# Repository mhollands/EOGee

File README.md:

# EOGee
PCB and code for capturing electrooculograms (EOG).

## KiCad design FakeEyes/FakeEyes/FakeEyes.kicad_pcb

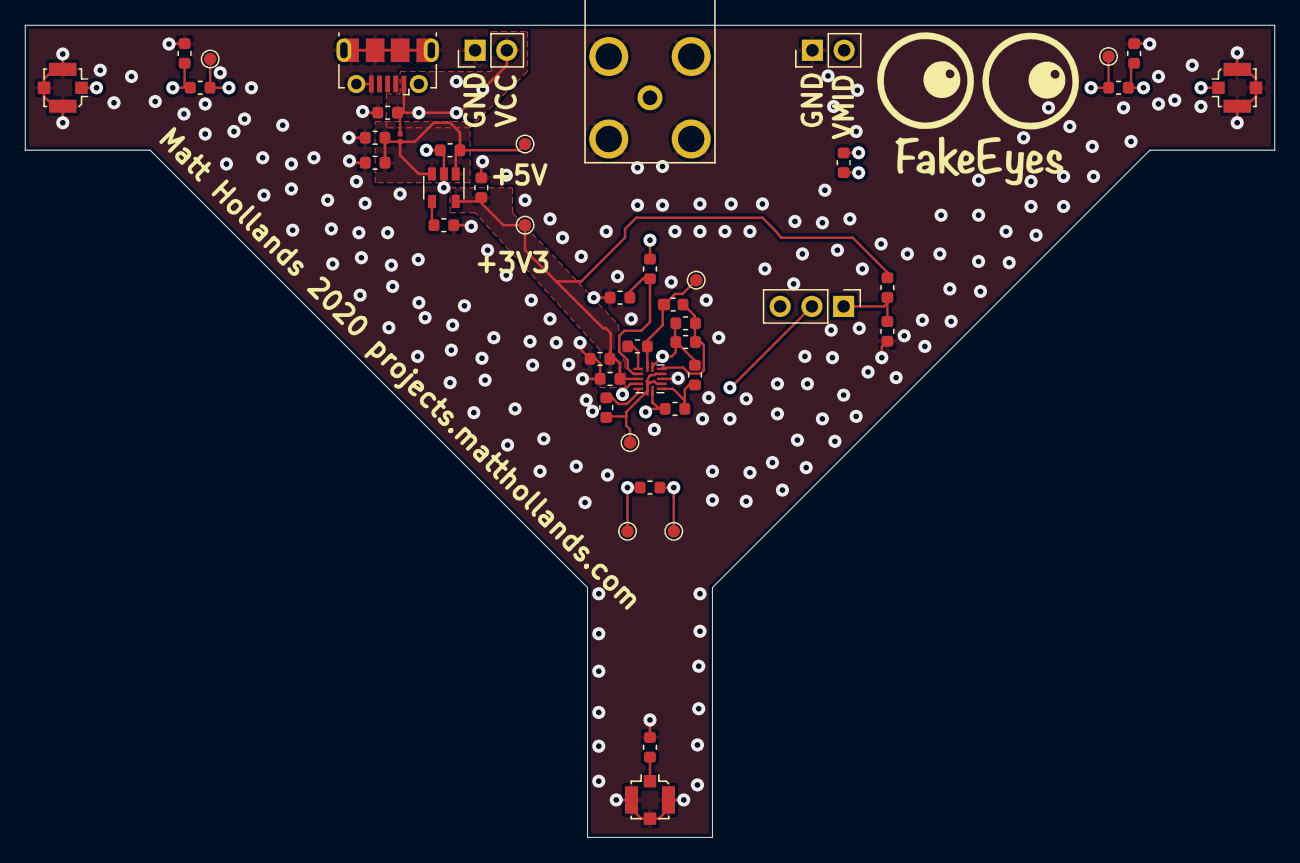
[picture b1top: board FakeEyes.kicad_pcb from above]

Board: 4 copper layers, 100.0 x 65.0 mm, 45 parts (0 on the bottom side), 22 nets.

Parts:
C1, C7: 1u; C_0603_1608Metric
C2: 10n; C_0603_1608Metric
C3, C8: 100n; C_0603_1608Metric
C4: 4.7u; C_0603_1608Metric
C5: 100p; C_0603_1608Metric
C6: 2.2u; C_0603_1608Metric
C9: 1232n; C_0603_1608Metric
C10: C; C_0603_1608Metric
J1: USB_B_Micro; USB_Micro-B_Molex-105017-0001
J2, J4: Conn_01x02; PinHeader_1x02_P2.54mm_Vertical
J3: TE Connectivity AMP Connectors 5-1634513-1; TE_5-1634513-1
J5, J6, J7: Conn_Coaxial; U.FL_Molex_MCRF_73412-0110_Vertical
JP1: Jumper_NC_Dual; PinHeader_1x03_P2.54mm_Vertical
L1: BK0603HS330-T; L_0201_0603Metric
R1, R2, R3, R4, R5, R6: 10k; R_0603_1608Metric
R7: 2.2M; R_0603_1608Metric
R8, R9, R10: 1k; R_0603_1608Metric
R11, R12, R13, R15, R16: 0R; R_0603_1608Metric
R14: R; R_0603_1608Metric
TP1, TP2, TP3, TP4, TP5, TP6, TP7, TP8: TestPoint; TestPoint_Pad_D1.0mm
U1: AP2210K-3.3TRG1; SOT-23-5
U2: TLV9004xRUCR; Texas_S-PX2QFN-14

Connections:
+3V3: C6.1, C7.1, C8.1, R1.1, TP2.1, U1.5, U2.3
+5V: C1.1, C3.1, C4.1, L1.2, TP1.1, U1.1, U1.3
GND: C1.2, C2.2, C3.2, C4.2, C5.2, C6.2, C7.2, C8.2, C10.2, J1.5, J1.6, J2.1, J3.2, J4.1, J5.2, J6.2, J7.2, R2.2, R11.2, R15.1, R16.1, U1.2, U2.10
unnamed: C2.1, J1.1, J2.2, L1.1
unnamed: C5.1, U1.4
unnamed: C9.1, R8.1, R9.2, R12.2, TP5.1, U2.13
unnamed: C9.2, R7.1, R8.2, U2.12
unnamed: C10.1, R3.1, U2.2
unnamed: J3.1, R3.2
unnamed: J4.2, R4.1
unnamed: J5.1, R12.1, R14.1, R15.2, TP7.1
unnamed: J6.1, R13.1, R14.2, R16.2, TP8.1
unnamed: J7.1, R11.1
unnamed: JP1.1, R1.2, R2.1
unnamed: JP1.2, U2.4
unnamed: JP1.3, R4.2
unnamed: R5.1, R7.2, TP3.1, U2.14
unnamed: R5.2, U2.1
unnamed: R6.1, TP4.1, U2.6, U2.9, U2.11
unnamed: R6.2, U2.5
unnamed: R10.1, R13.2, TP6.1, U2.7
unnamed: R9.1, R10.2, U2.8

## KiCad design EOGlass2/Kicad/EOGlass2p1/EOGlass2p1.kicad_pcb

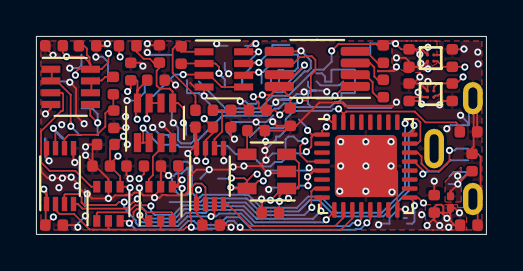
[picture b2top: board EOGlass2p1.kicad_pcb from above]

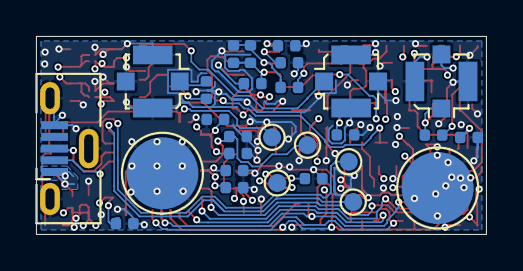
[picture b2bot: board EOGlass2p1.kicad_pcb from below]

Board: 4 copper layers, 25.0 x 11.0 mm, 73 parts (28 on the bottom side), 41 nets.

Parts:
C1, C10: 4.7uF; C_0402_1005Metric
C2, C3, C7, C11, C13, C17, C18, C23, C27, C28, C29, C30, C31, C34, C35, C36: 1uF; C_0402_1005Metric
C4, C5, C8, C15, C19, C21, C25, C26, C32, C33: 100nF; C_0402_1005Metric
C6, C9: 10nF; C_0402_1005Metric
C12: 100pF; C_0402_1005Metric
C14: 2.2uF; C_0402_1005Metric
C16: 10uF; C_0402_1005Metric
C20: 560pF; C_0402_1005Metric
C22, C24: C; C_0402_1005Metric
H1, H2: MountingHole_Pad; TestPoint_Pad_D4.0mm
J1: USB_B_Micro; USB_Micro-B_Molex-105133-0001
J2, J3, J4: Conn_Coaxial; U.FL_Molex_MCRF_73412-0110_Vertical
L1: L; L_0201_0603Metric
R1: 750R; R_0402_1005Metric
R2, R3: 47k; R_0402_1005Metric
R4, R5, R9, R13: 10k; R_0402_1005Metric
R6: 1M; R_0402_1005Metric
R7: 100k; R_0402_1005Metric
R8: 2.2M; R_0402_1005Metric
R10: 15k; R_0402_1005Metric
R11, R12: R; R_0402_1005Metric
TP1, TP2, TP3, TP4, TP5: TestPoint; TestPoint_Pad_D1.0mm
U1: LP5907UVX-3.3_NOPB
U2: AP2210K-3.3TRG1; SOT-23-5
U3: STM32L412kx; QFN-32-1EP_5x5mm_P0.5mm_EP3.45x3.45mm
U4: AD8226ARMZ; MSOP-8_3x3mm_P0.65mm
U5, U6, U7: LMV358A; SOT-23-8
U8, U11: DAC7311IDCKR; SOT-363_SC-70-6
U9, U10: ADS7042xDCU; VSSOP-8_2.3x2mm_P0.5mm
U12: LP5907UVX-4.5_NOPB

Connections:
+3.3VA: C13.1, C17.1, C18.1, C19.1, C21.1, C23.1, C25.1, C27.1, C29.1, C30.1, C31.1, C32.1, C33.1, R4.1, U1.A2, U5.8, U6.8, U7.8, U8.4, U9.7, U10.7, U11.4
+3V3: C1.1, C4.1, C5.1, C7.1, C9.1, C14.1, C28.1, C34.1, TP5.1, U2.5, U3.1, U3.5, U3.17, U9.1, U10.1
+4V5: C15.1, C16.1, C36.1, U4.8, U12.A2
/ADC1_CS: U3.10, U10.4
/ADC2_CS: U3.8, U9.4
/BOOT: R13.1, TP1.1, U3.31
/DAC1_CS: U3.9, U8.1
/DAC2_CS: U3.7, U11.1
/DRIVE: J4.1, R6.2, U5.5
/NRST: C26.1, TP4.1, U3.4
/SIGNAL_N: J3.1, R3.1
/SIGNAL_P: J2.1, R2.2
/SPI1_MISO: U3.12, U9.3, U10.3
/SPI1_MOSI: U3.13, U8.3, U11.3
/SPI1_SCK: U3.11, U8.2, U9.2, U10.2, U11.2
/SWDCLK: TP3.1, U3.24
/SWDIO: TP2.1, U3.23
/USB_DM: J1.2, U3.21
/USB_DP: J1.3, U3.22
/Vmid: U6.6, U6.7, U7.3, U7.5
/Vref: U4.6, U6.1, U6.2
GND: C1.2, C2.2, C3.2, C4.2, C5.2, C6.2, C7.2, C8.2, C9.2, C10.2, C11.2, C12.2, C13.2, C14.2, C15.2, C16.2, C17.2, C18.2, C19.2, C21.2, C22.2, C23.2, C24.2, C25.2, C26.2, C27.2, C28.2, C29.2, C30.2, C31.2, C32.2, C33.2, C34.2, C35.2, C36.2, H1.1, H2.1, J1.5, J1.6, J2.2, J3.2, J4.2, R5.2, R13.2, U1.B2, U2.2, U3.16, U3.32, U3.33, U4.5, U5.4, U6.4, U7.4, U8.5, U9.5, U9.8, U10.5, U10.8, U11.5, U12.B2
unnamed: C6.1, J1.1, L1.1
unnamed: C12.1, U2.4
unnamed: C20.1, R8.1, R9.2, U7.7
unnamed: C20.2, R7.1, R8.2, U7.6
unnamed: C22.1, R11.1, U9.6
unnamed: C24.1, R12.1, U10.6
unnamed: C35.1, R4.2, R5.1, U6.5
unnamed: R1.1, U4.2
unnamed: R1.2, U4.3
unnamed: R2.1, U4.1
unnamed: R3.2, U4.4
unnamed: R6.1, U5.1, U5.2
unnamed: R7.2, U4.7
unnamed: R10.1, R12.2, U7.1
unnamed: R9.1, R10.2, U7.2
unnamed: R11.2, U5.6, U5.7
unnamed: U6.3, U8.6
unnamed: U5.3, U11.6
VBUS: C2.1, C3.1, C8.1, C10.1, C11.1, L1.2, U1.A1, U1.B1, U2.1, U2.3, U12.A1, U12.B1

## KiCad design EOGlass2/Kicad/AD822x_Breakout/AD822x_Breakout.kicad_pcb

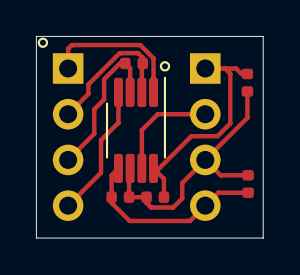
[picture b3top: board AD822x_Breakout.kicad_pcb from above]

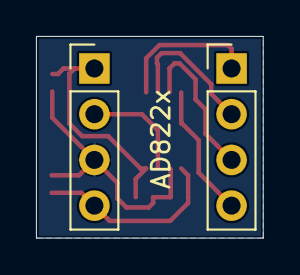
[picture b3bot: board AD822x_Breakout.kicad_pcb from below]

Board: 2 copper layers, 12.6 x 11.2 mm, 8 parts (2 on the bottom side), 8 nets.

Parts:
C1, C3: 100n; C_0402_1005Metric
C2, C4: 10u; C_0402_1005Metric
J1, J2: Conn_01x04; PinHeader_1x04_P2.54mm_Vertical
R1: R; R_0402_1005Metric
U1: AD8226ARMZ; MSOP-8_3x3mm_P0.65mm

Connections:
/In+: J1.4, U1.4
/In-: J1.1, U1.1
/Rg1: J1.2, R1.1, U1.2
/Rg2: J1.3, R1.2, U1.3
/V+: C1.2, C2.2, J2.1, U1.8
/V-: C3.2, C4.2, J2.4, U1.5
/Vout: J2.2, U1.7
/Vref: C1.1, C2.1, C3.1, C4.1, J2.3, U1.6

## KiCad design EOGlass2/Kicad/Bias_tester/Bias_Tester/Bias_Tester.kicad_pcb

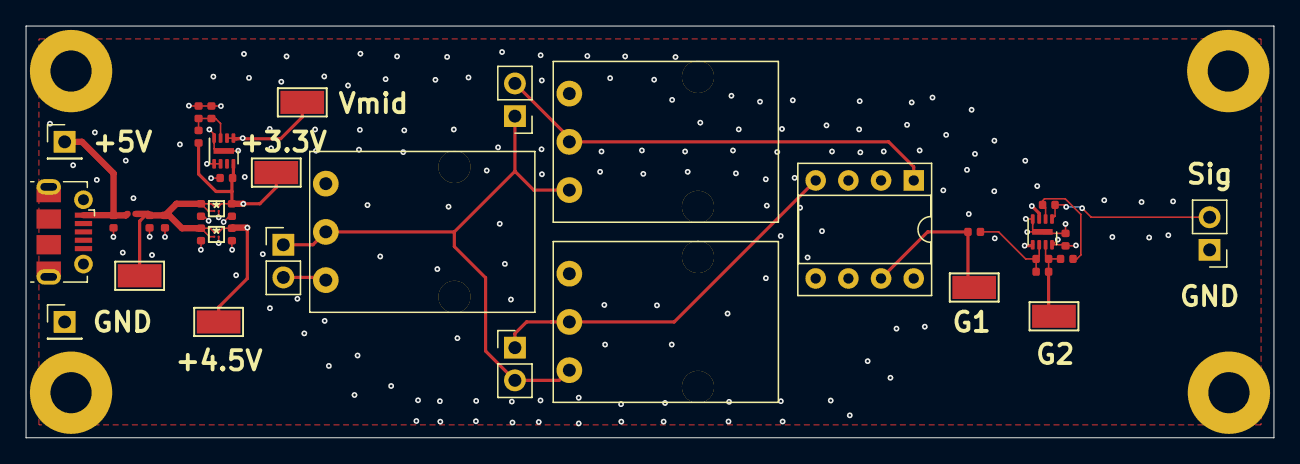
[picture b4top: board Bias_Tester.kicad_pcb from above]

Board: 4 copper layers, 97.0 x 32.0 mm, 43 parts (0 on the bottom side), 15 nets.

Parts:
C1, C2, C3: C; C_0402_1005Metric
C4, C10: 100n; C_0402_1005Metric
C5, C6, C8, C9, C11: 1u; C_0402_1005Metric
C7: 560p; C_0402_1005Metric
H1, H2, H3, H4: MountingHole_Pad; MountingHole_3.2mm_M3_Pad
J1: USB_B_Micro; USB_Micro-B_Molex-105017-0001
J2, J3: Conn_01x01; PinHeader_1x01_P2.54mm_Vertical
JP1, JP2, JP3: Jumper_NC_Small; PinHeader_1x02_P2.54mm_Vertical
L1: L; L_0201_0603Metric
R1: 100k; R_0402_1005Metric
R2, R3, R5: 10k; R_0402_1005Metric
R4: 2.2M; R_0402_1005Metric
R6: 15k; R_0402_1005Metric
RV1, RV2, RV3: R_POT; PDB12-H4301-105BF
TP1, TP2, TP4, TP5, TP6, TP7: TestPoint; TestPoint_Keystone_5015_Micro-Minature
TP3: TestPoint_2Pole; PinHeader_1x02_P2.54mm_Vertical
U1, U5: TSZ122; TSZ122_DFN8
U2: AD8226ARMZ; DIP-8_W7.62mm_Socket
U3: YKE4_TEX; LP5907UVX-3.3_NOPB
U4: YKE4_TEX; LP5907UVX-4.5_NOPB

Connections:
+3V3: C4.1, C8.2, C10.1, R2.1, TP6.1, U1.8, U3.A2, U5.8
/Vmid: TP7.1, U1.1, U1.2, U2.6, U5.3, U5.5
GND: C1.2, C2.2, C3.2, C4.2, C5.1, C6.2, C8.1, C9.1, C10.2, C11.1, H1.1, H2.1, H3.1, H4.1, J1.5, J1.6, J2.1, JP2.2, R3.2, RV2.3, TP3.1, U1.4, U1.5, U1.6, U1.9, U2.5, U3.B2, U4.B2, U5.4, U5.9
unnamed: C1.1, J1.1, J3.1, L1.1
unnamed: C6.1, R2.2, R3.1, U1.3
unnamed: C7.1, R4.1, R5.2, TP2.1, U5.7
unnamed: C7.2, R1.1, R4.2, U5.6
unnamed: JP1.1, JP2.1, JP3.2, RV1.3, RV2.2, RV3.3
unnamed: JP1.2, RV1.2, U2.1
unnamed: JP3.1, RV3.2, U2.4
unnamed: R1.2, TP1.1, U2.7
unnamed: R5.1, R6.2, U5.2
unnamed: R6.1, TP3.2, U5.1
VBUS: C2.1, C3.1, C5.2, C9.2, L1.2, TP4.1, U3.A1, U3.B1, U4.A1, U4.B1
~: C11.2, TP5.1, U2.8, U4.A2

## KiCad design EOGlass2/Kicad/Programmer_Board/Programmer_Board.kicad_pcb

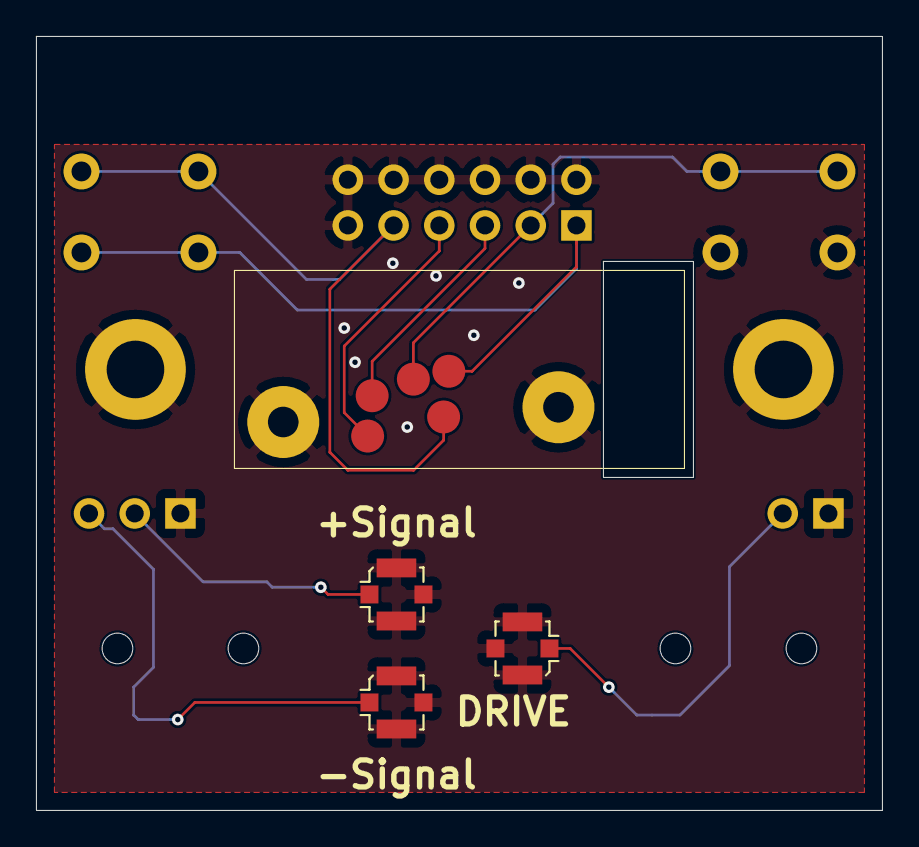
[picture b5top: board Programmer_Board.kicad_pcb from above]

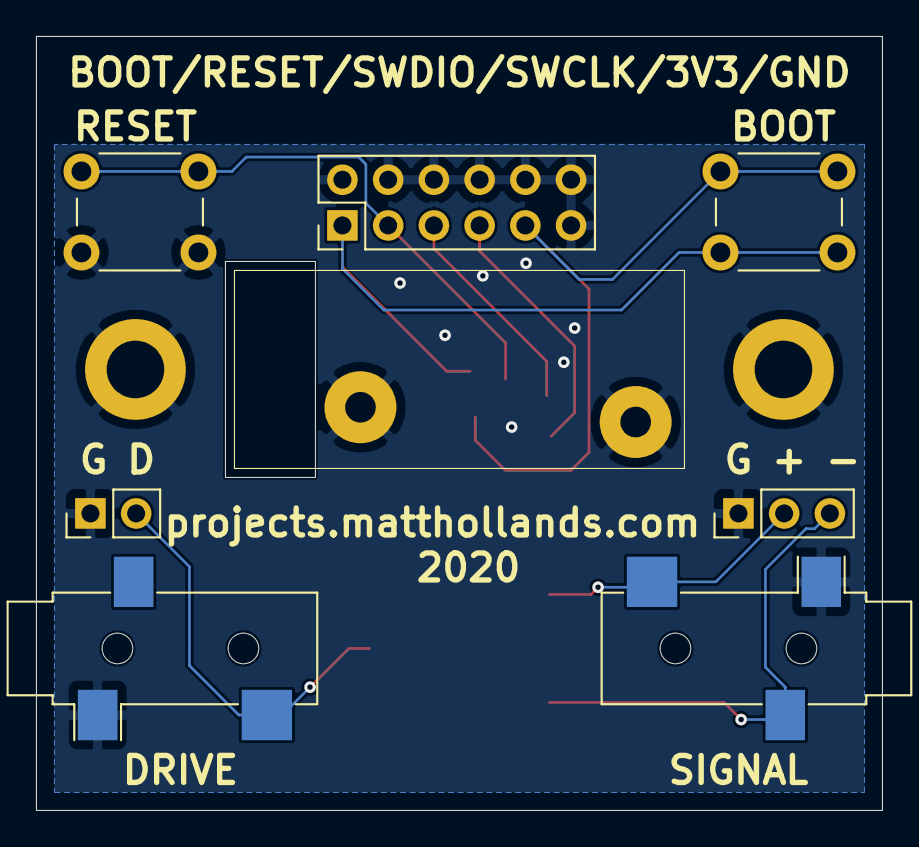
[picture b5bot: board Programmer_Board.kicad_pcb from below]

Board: 2 copper layers, 47.0 x 43.0 mm, 19 parts (7 on the bottom side), 9 nets.

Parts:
H1, H2: MountingHole_Pad; Wurth_97730256330R
H3, H4: MountingHole_Pad; MountingHole_3.2mm_M3_DIN965_Pad
J1: Conn_02x06_Odd_Even; PinHeader_2x06_P2.54mm_Vertical
J2: AudioJack2; Jack_3.5mm_CUI_SJ-3523-SMT_Horizontal
J3: AudioJack3; Jack_3.5mm_CUI_SJ-3523-SMT_Horizontal
J4, J5, J6: Conn_Coaxial; U.FL_Molex_MCRF_73412-0110_Vertical
J7: Conn_01x03; PinHeader_1x03_P2.54mm_Vertical
J8: Conn_01x02; PinHeader_1x02_P2.54mm_Vertical
SW1, SW2: SW_Push_45deg; SW_PUSH_6mm
TP1, TP2, TP3, TP4, TP5: TestPoint; Preci-Dip_90174-AS

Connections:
+3V3: J1.9, SW2.2, TP1.1
/BOOT: J1.1, SW2.1, TP3.1
/DRIVE: J2.T, J6.1, J8.2
/RESET: J1.3, SW1.2, TP2.1
/SIGNAL_N: J3.R, J5.1, J7.3
/SIGNAL_P: J3.T, J4.1, J7.2
/SWCLK: J1.7, TP4.1
/SWDIO: J1.5, TP5.1
GND: H1.1, H2.1, H3.1, H4.1, J1.2, J1.4, J1.6, J1.8, J1.10, J1.11, J1.12, J2.S, J3.S, J4.2, J5.2, J6.2, J7.1, J8.1, SW1.1

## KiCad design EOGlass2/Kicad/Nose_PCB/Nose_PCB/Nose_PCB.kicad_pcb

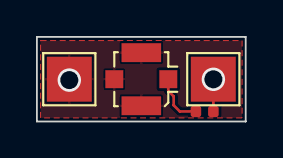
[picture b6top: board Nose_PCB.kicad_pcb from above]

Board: 2 copper layers, 11.6 x 4.7 mm, 4 parts (0 on the bottom side), 3 nets.

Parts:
J1: Conn_Coaxial; U.FL_Molex_MCRF_73412-0110_Vertical
J2, J3: Conn_01x01_Female; TestPoint_Pad_2.5x2.5mm
R1: 0; R_0402_1005Metric

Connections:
/SENSE: J2.1, R1.1
GND: J1.2, J3.1
unnamed: J1.1, R1.2

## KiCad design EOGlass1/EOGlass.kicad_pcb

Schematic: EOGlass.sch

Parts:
C102, C107, C108, C117, C118, C121, C123, C124, C127: 100nF; C_0402_1005Metric
C103, C115: 10nF; C_0402_1005Metric
C104, C109, C119, C125: 4.7uF; C_0402_1005Metric
C110: 10uF; C_0402_1005Metric
C111, C116, C122, C128: 1uF; C_0402_1005Metric
C112: 2.2uF; C_0402_1005Metric
C114: 560pF; C_0402_1005Metric
C120: C; C_0402_1005Metric
C126: 100pF; C_0402_1005Metric
J1, J2, J3: Conn_01x01_Female; TestPoint_Keystone_5019_Minature
J101: USB_B_Micro; USB_Micro-B_Molex-105133-0001
L101, L102: BK0603HS330-T; L_0201_0603Metric
R101: 750R; C_0402_1005Metric
R102, R103: 47k; C_0402_1005Metric
R104, R105, R108, R109: 10k; C_0402_1005Metric
R106: 100k; C_0402_1005Metric
R107: 2.2M; C_0402_1005Metric
R113: 4k7; C_0402_1005Metric
R114: R; C_0402_1005Metric
U1: LMV324; SOIC-14_3.9x8.7mm_P1.27mm
U102: AD8226ARMZ; MSOP-8_3x3mm_P0.65mm
U103: AP2210K-3.3; SOT-23-5; MPN AP2210K
U104: MCP41010; SOIC-8_3.9x4.9mm_P1.27mm
U105: STM32F072CBTx; LQFP-48_7x7mm_P0.5mm

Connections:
+3.3VA: C102.1, C104.1, C108.1, C110.1, C115.1, C116.1, C127.1, C128.1, L101.2, R104.1, U1.4, U102.8 (Vs+), U105.9
+3V3: C112.1, C117.1, C119.1, C121.1, C123.1, C124.1, C125.1, L101.1, U103.5, U104.8, U105.1, U105.24, U105.36, U105.48
/MCP_CS: U104.1, U105.38
/MOSI: U104.3, U105.41
/SCK: U104.2, U105.39
/SIGNAL_N: J2.1, R103.2
/SIGNAL_P: J1.1, R102.2
/USB_DM: J101.2 (D-), U105.32
/USB_DP: J101.3 (D+), U105.33
/VADC: C120.1, R114.1, U105.11
/VREF_DAC: U1.12, U105.15, U105.16
GND: C102.2, C103.2, C104.2, C107.2, C108.2, C109.2, C110.2, C111.2, C112.2, C115.2, C116.2, C117.2, C118.2, C119.2, C120.2, C121.2, C122.2, C123.2, C124.2, C125.2, C126.2, C127.2, C128.2, J3.1, J101.5 (GND), J101.6 (Shield), R105.2, R109.2, U1.11, U102.5 (Vs-), U103.2, U104.4, U105.8, U105.23, U105.35, U105.47
unnamed: C103.1, J101.1 (VBUS), L102.1
unnamed: C107.1, C109.1, C111.1, L102.2, U103.1, U103.3
unnamed: C114.1, R107.1, R108.2, U1.7
unnamed: C114.2, R106.1, R107.2, U1.6
unnamed: C118.1, U105.7
unnamed: C122.1, R104.2, R105.1, U1.3
unnamed: C126.1, U103.4
unnamed: R101.1, U102.2 (Rg)
unnamed: R101.2, U102.3 (Rg)
unnamed: R102.1, U102.1 (-)
unnamed: R103.1, U102.4 (+)
unnamed: R106.2, U102.7
unnamed: R108.1, R113.2, U1.9
unnamed: R109.1, U105.44
unnamed: R113.1, U104.7
unnamed: R114.2, U1.8, U104.5, U104.6
unnamed: U1.1, U1.2, U1.5, U1.10
unnamed: U1.13, U1.14, U102.6 (Ref)

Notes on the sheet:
Matt Hollands 2020 projects.matthollands.com
R113 necessary to limit MCP41010 wiper current to less than +/-1mA assuming maximum 3.3V on U101D pin 14 and ground on U101D pin 13.
Select R114 and C120 based on Analog Dialogue 46-12 by Alan Walsh at ADI
Vdda Decoupling
Vdd Decoupling
Vddio2 Decoupling
Digikey PN: 609-4618-1-ND

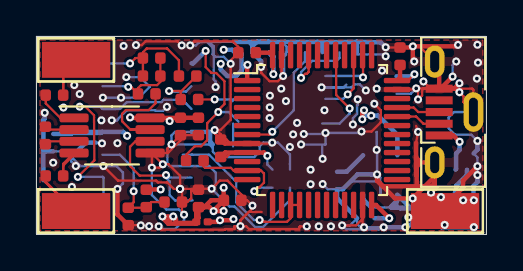
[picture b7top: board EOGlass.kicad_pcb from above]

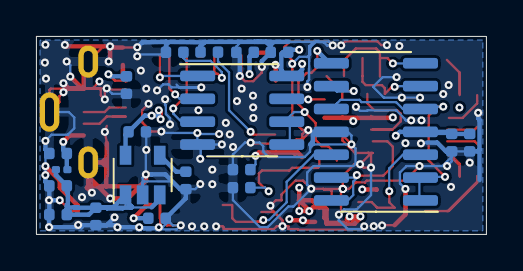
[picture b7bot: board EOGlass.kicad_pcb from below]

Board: 4 copper layers, 25.0 x 11.0 mm, 46 parts (20 on the bottom side), 30 nets.

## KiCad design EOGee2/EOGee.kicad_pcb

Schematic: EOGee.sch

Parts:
C101, C102, C107, C108, C117, C118, C121, C123, C124, C127: 100nF; C_0603_1608Metric
C103, C115: 10nF; C_0603_1608Metric
C104, C109, C119, C125: 4.7uF; C_0603_1608Metric
C105, C106, C110, C113: 10uF; C_0603_1608Metric
C111, C116, C122, C128: 1uF; C_0603_1608Metric
C112: 2.2uF; C_0603_1608Metric
C114: 560pF; C_0603_1608Metric
C120: C; C_0603_1608Metric
C126: 100pF; C_0603_1608Metric
D101, D102, D103: LED; LED_0603_1608Metric
H101, H102, H103, H104: MountingHole_Pad; MountingHole_3.2mm_M3_DIN965_Pad
J101: USB_B_Micro; USB_Micro-B_Molex-105017-0001
J102: AudioJack3; Jack_3.5mm_CUI_SJ-3523-SMT_Horizontal
J103, J104, J105: AudioJack2; Jack_3.5mm_CUI_SJ-3523-SMT_Horizontal
J106: Conn_01x02; PinHeader_1x02_P2.54mm_Vertical
JP101, JP102: Jumper_NC_Small; PinHeader_1x02_P2.54mm_Vertical
JP103, JP104, JP105: Jumper_3_Bridged12; PinHeader_1x03_P2.54mm_Vertical
JP106: Jumper_NO_Small; PinHeader_1x02_P2.54mm_Vertical
L101, L102: BK0603HS330-T; L_0201_0603Metric
R101: 16k; R_0603
R102, R103: 47k; R_0603
R104, R105, R106, R108: 10k; R_0603
R107: 2.2M; R_0603
R109, R115: 10k; R_0603_1608Metric
R110, R111, R112: 750; R_0603
R113: 4k7; R_0603_1608Metric
R114, R116, R117: R; R_0603_1608Metric
SW101, SW102: SW_Push_45deg; SW_SPST_B3U-1000P
TP101, TP102, TP103, TP104: TestPoint_2Pole; TestPoint_2Pads_Pitch2.54mm_Drill0.8mm
U101: LMV358; SOIC-8_3.9x4.9mm_P1.27mm
U102: AD8226ARMZ; MSOP-8_3x3mm_P0.65mm
U103: AP2210K-3.3; SOT-23-5; MPN AP2210K
U104: MCP41010; SOIC-8_3.9x4.9mm_P1.27mm
U105: STM32F072CBTx; LQFP-48_7x7mm_P0.5mm
U106: OP2177ARZ-REEL; SOIC-8_3.9x4.9mm_P1.27mm

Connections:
+3.3VA: C101.1, C102.1, C104.1, C105.1, C108.1, C110.1, C115.1, C116.1, C127.1, C128.1, J106.2, L101.2, R104.1, U101.8, U102.8 (Vs+), U105.9, U106.8
+3V3: C112.1, C117.1, C119.1, C121.1, C123.1, C124.1, C125.1, L101.1, R112.1, SW101.1, U103.5, U104.8, U105.1, U105.24, U105.36, U105.48
/MCP_CS: U104.1, U105.38
/MISO: R115.1, U105.40
/MOSI: U104.3, U105.41
/SCK: U104.2, U105.39
/SIGNAL_N: J102.R, J104.T, JP103.1, JP104.3
/SIGNAL_P: J102.T, J103.T, JP103.3, JP104.1
/USB_DM: J101.2 (D-), U105.32
/USB_DP: J101.3 (D+), U105.33
/VADC: C120.1, R114.1, U105.11
/VREF_DAC: JP105.1, U105.15, U105.16
GND: C101.2, C102.2, C103.2, C104.2, C106.2, C107.2, C108.2, C109.2, C110.2, C111.2, C112.2, C115.2, C116.2, C117.2, C118.2, C119.2, C120.2, C121.2, C122.2, C123.2, C124.2, C125.2, C126.2, C127.2, C128.2, D101.1 (K), D102.1 (K), D103.1 (K), H101.1, H102.1, H103.1, H104.1, J101.5 (GND), J101.6 (Shield), J102.S, J105.S, J105.T, J106.1, JP101.2, JP102.2, R105.2, R109.2, R115.2, R116.1, R117.2, SW102.1, TP101.2, TP102.2, TP103.2, TP104.2, U101.4, U102.5 (Vs-), U103.2, U104.4, U105.8, U105.23, U105.35, U105.47, U106.4
unnamed: C103.1, J101.1 (VBUS), L102.1
unnamed: C105.2, C106.1, U101.3, U101.5, U106.6, U106.7
unnamed: C107.1, C109.1, C111.1, L102.2, U103.1, U103.3
unnamed: C113.1, C114.2, R107.2, U101.2
unnamed: C113.2, R106.1
unnamed: C114.1, R107.1, R108.2, TP102.1, U101.1
unnamed: C118.1, SW102.2, U105.7
unnamed: C122.1, JP105.3, R104.2, R105.1, U106.5
unnamed: C126.1, U103.4
unnamed: D101.2 (A), R110.2
unnamed: D102.2 (A), R111.2
unnamed: D103.2 (A), R112.2
unnamed: J103.S, JP101.1
unnamed: J104.S, JP102.1
unnamed: JP103.2, R102.2
unnamed: JP104.2, R103.2
unnamed: JP105.2, U106.3
unnamed: JP106.1, R113.1, U104.7
unnamed: JP106.2, R114.2, TP103.1, U101.7, U104.5, U104.6
unnamed: R101.1, U102.2 (Rg)
unnamed: R101.2, U102.3 (Rg)
unnamed: R102.1, R116.2, U102.1 (-)
unnamed: R103.1, R117.1, U102.4 (+)
unnamed: R106.2, TP101.1, U102.7
unnamed: R108.1, R113.2, U101.6
unnamed: R109.1, SW101.2, U105.44
unnamed: R110.1, U105.3
unnamed: R111.1, U105.2
unnamed: TP104.1, U102.6 (Ref), U106.1, U106.2

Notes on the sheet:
Matt Hollands 2020 projects.matthollands.com
R113 necessary to limit MCP41010 wiper current to less than +/-1mA assuming maximum 3.3V on U101D pin 14 and ground on U101D pin 13.
Select R114 and C120 based on Analog Dialogue 46-12 by Alan Walsh at ADI
Vdda Decoupling
Vdd Decoupling
Vddio2 Decoupling
Digikey PN: CP-3523MJCT-ND
Digikey PN: SC1489-1-ND
Digikey PN: 609-4618-1-ND
Digikey PN: SW1020CT-ND

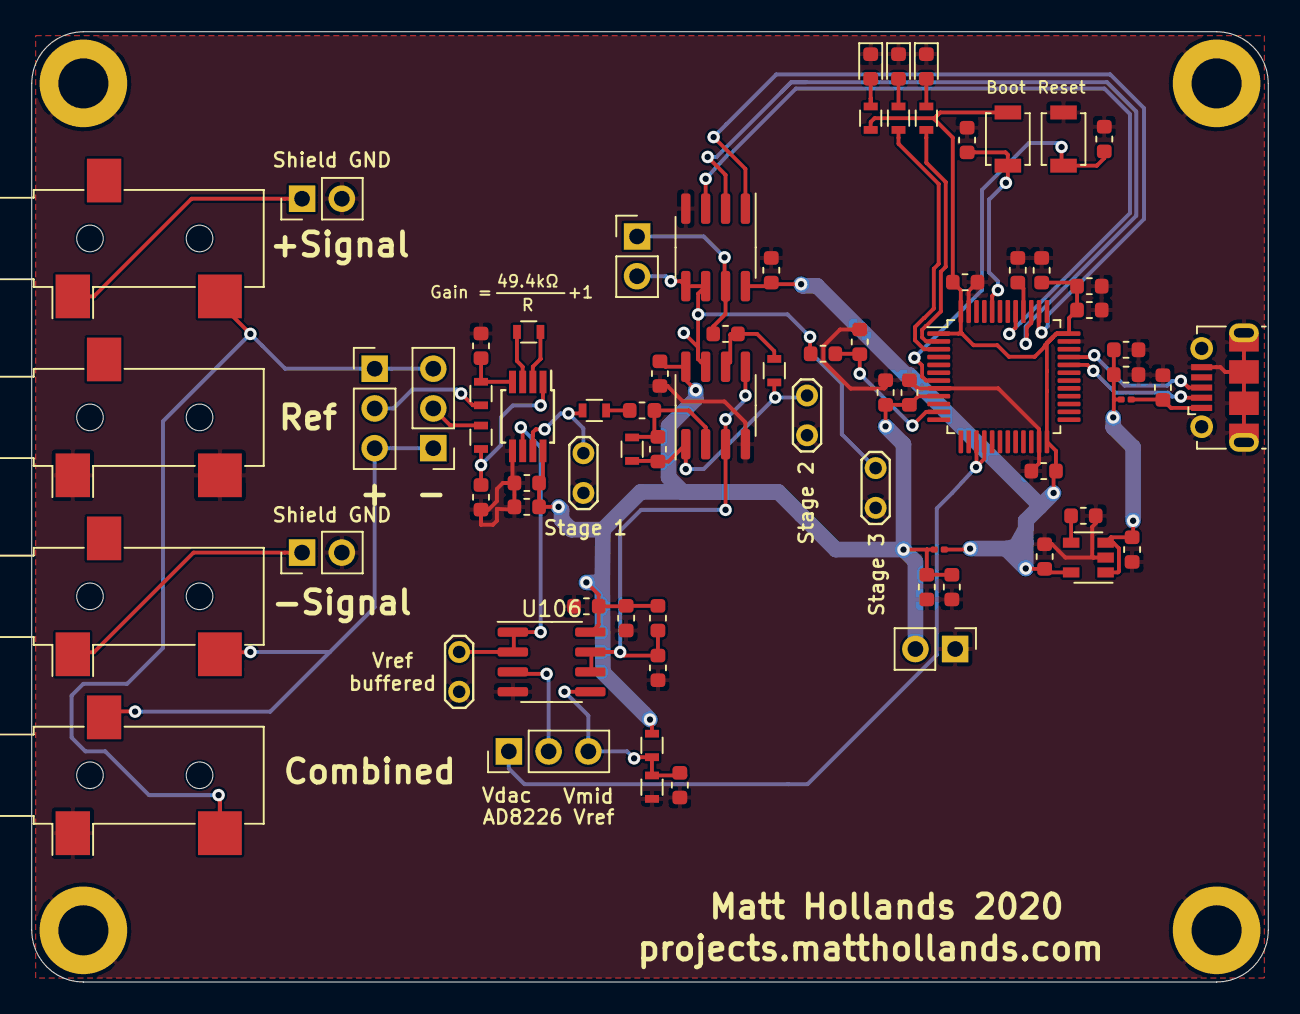
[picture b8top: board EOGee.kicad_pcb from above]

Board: 2 copper layers, 79.0 x 60.7 mm, 78 parts (0 on the bottom side), 42 nets.

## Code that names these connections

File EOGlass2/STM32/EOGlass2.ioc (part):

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Mcu.Name=STM32L412KBUx
Mcu.Package=UFQFPN32
Mcu.UserName=STM32L412KBUx
PA1.GPIOParameters=PinState,GPIO_Label,GPIO_ModeDefaultOutputPP
PA1.GPIO_Label=CS_DRIVE
PA1.GPIO_ModeDefaultOutputPP=GPIO_MODE_OUTPUT_PP
PA1.PinState=GPIO_PIN_SET
PA1.Signal=GPIO_Output
PA11.Mode=Device
PA11.Signal=USB_DM
PA12.Mode=Device
PA12.Signal=USB_DP
PA13\ (JTMS/SWDIO).Mode=Serial_Wire
PA13\ (JTMS/SWDIO).Signal=SYS_JTMS-SWDIO
PA14\ (JTCK/SWCLK).Mode=Serial_Wire
PA14\ (JTCK/SWCLK).Signal=SYS_JTCK-SWCLK
PA2.GPIOParameters=PinState,GPIO_Label
PA2.GPIO_Label=CS_SENSE
PA2.PinState=GPIO_PIN_SET
PA2.Signal=GPIO_Output
PA3.GPIOParameters=PinState,GPIO_Label,GPIO_ModeDefaultOutputPP
PA3.GPIO_Label=CS_REF
PA3.GPIO_ModeDefaultOutputPP=GPIO_MODE_OUTPUT_PP
PA3.PinState=GPIO_PIN_SET
PA3.Signal=GPIO_Output
PA4.GPIOParameters=PinState,GPIO_Label
PA4.GPIO_Label=CS_SIGNAL
PA4.PinState=GPIO_PIN_SET
PA4.Signal=GPIO_Output
PA5.GPIOParameters=GPIO_PuPd
PA5.GPIO_PuPd=GPIO_PULLDOWN
PA5.Mode=Full_Duplex_Master
PA5.Signal=SPI1_SCK
PA6.Mode=Full_Duplex_Master
PA6.Signal=SPI1_MISO
PA7.Mode=Full_Duplex_Master
PA7.Signal=SPI1_MOSI
PH3-BOOT0\ (BOOT0).GPIOParameters=GPIO_Label
PH3-BOOT0\ (BOOT0).GPIO_Label=DEBUG
PH3-BOOT0\ (BOOT0).Signal=GPIO_Output
RCC.HSE_VALUE=8000000
RCC.SYSCLKFreq_VALUE=72000000
RCC.SYSCLKSource=RCC_SYSCLKSOURCE_PLLCLK
board=custom

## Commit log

2020-01-20 add initial schematic
2020-02-18 moved to STM32MXCubeIDE
2020-02-18 add name to schematic:
2020-02-19 remove stupid metadata files
2020-02-19 add ADC and timer
2020-02-19 Timer approximately 10hz, start ADC. ADC complete copy into buffer. buffer full send via serial.
2020-02-19 turn on green LED if no space in buffer at any point
2020-02-19 sample around 70hz
2020-02-19 (i mean 700hz). Python viewer now converts 8 bit data into 16 bit data and displays it. Limit to 1000 samples on screen
2020-02-23 fix bug where bytes were in the wrong order
2020-02-24 plot in volts and samples. Do fourier transform. Do 60hz notch filter
2020-02-24 add initial glasses model
2020-02-26 move to new EOGee1 folder
2020-02-26 moved everythign to EOGee1 folder
2020-02-26 started work on active probe design
2020-02-27 added amplifier stages and filtering
2020-03-09 add some 3d models
2020-03-09 models, active probe, ltspice model
2020-03-09 started analysis of EOGee1
2020-03-22 Add siggen adapter files
2020-03-28 add circuit analysis for EOG1
2020-03-28 makefile changes
2020-03-28 added 3d printed plastic snap models
2020-03-28 add EOG2 kicad design
2020-03-31 started implementations of f behrens alg
2020-04-03 rewrite f behrens with better support for per sample calculations in a way that doesn't hurt the brain
2020-04-03 added MSF trigger on D2Y crossing NSigma threshold
2020-04-04 add F1 flag
2020-04-04 add playback from .npy file and also headroom to plots
2020-04-04 better fake saccade
2020-04-04 add pause function and also Fmon flag
2020-04-04 add f2 flag
2020-04-05 added F3 flag and reset flags when saccade complete
2020-04-12 show noise stats at the end of viewer
2020-04-12 add noise measurements from EOG1
2020-04-12 tidying up
2020-04-12 add eog2 housing model and base model
2020-04-14 add empty stm32 fw
2020-04-14 add example code for leds and DAC
2020-04-15 :add code to set MCP41010 resistance
2020-04-15 replace OP2177 with LMV358 because does not support 3.3V rail
2020-04-17 add code from EOGee1 to stream ADC over USB
2020-04-18 add code to change dac to center signal at 2048 at startup
2020-04-19 add code to center DAC when we hit limits:
2020-04-19 Center dac command is no longer needed
2020-04-19 stream DAC codes over USB too
2020-04-19 fix typo
2020-04-19 handle serial connection more gracefully during connect and disconnect
2020-04-23 Insert correct resistor values for gains
2020-04-24 add f_brehrens to eogee2
2020-05-25 everything up to date
2020-05-25 add EOGee2 schematic
2020-06-01 add EOGlass1 files:
2020-06-21 add noise measureement data
2020-06-21 add images of EOGlass1
2020-06-21 random files
2020-06-21 fake saccade file for testing
2020-06-21 add PDF schematics for EOGlass1 and SigGenAdapter
2020-06-27 add sinewave dma to DAC_OUT2
2020-06-28 trigger EOG ADC conversion with timer1 automatically instead of calling from timer interrupt
2020-06-28 remove some doubkle files
2020-06-28 feedback DAC is now driven by DMA instead of software writes. This fixes bug where DAC channel 1 was set by software and DMA because its not possible for software to only set one DAC channel. Also di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
2020-06-28 change electrode sense frequency to 1khz
2020-06-29 change stim frequency to 300Hz
2020-07-06 add code to measure mult speed
2020-07-06 add code to generate sine wave data
2020-07-06 run ADC on DMA
2020-07-09 sample ADC3 too
2020-07-12 add demodulation (calculated every 500 samples which is a multiple of 60Hz and 300Hz)
2020-08-30 add eoglass2 design
2020-08-31 add EOGlass 2 code (not finished)
2020-08-31 function to package dac data in correct format
2020-08-31 add script to generate in phase and quad phase sine wave
2020-08-31 launch DAC conversion of sinewave from timer at 32khz
2020-08-31 mvoe drive dac stuff to its own function
2020-09-01 remove useless code and correct DRIVE REF CS pin labelling
2020-09-01 add code to switch between spi modes and basic code for checking ADC
2020-09-01 add bin
2020-09-02 change from cdc class to audio class
2020-09-02 change descriptor to make device an audio input
2020-09-02 going back to cdc
2020-09-02 send some dummy data over USB
2020-09-02 lower the USB interrupt priority so it doesn't mess with the SPI transactions
2020-09-03 add boot pin as debug. Add code for receiving sense adc data, but causing issue because spi is too slow. Slow down timer by 10x while we fix this issue
2020-09-06 use my own spi functions instead of HAL library becaused HAL library is too inefficient to complete 4 spi transactions in 31us allowed by 32000 timer. Add debug pin on BOOT0 pin.
2020-09-06 add sense adc read code and demodulate data. fixed >= comparison that meant sense and drive drifted out of phase. add python script to view demod data over usb
2020-09-06 add python code to calculate size of accumulators in bits
2020-09-06 optimise demod code to include only 32 and 16 bit maths and variables, instead of 64-bit
2020-09-06 add code to drive ref DAC.
2020-09-06 add code to handle signal read, downsample and store in buffer
2020-09-07 add code to stream signal
2020-09-07 generate signed sinewave instead of unsigned
2020-09-07 inphase and quadphase data stores as signed integer and converted on the fly
2020-09-08 remove code calculating max bit size for worst case demod input because it's too complex
2020-09-08 do demodulation in signed integers but report the value as unsigned over USB
2020-09-08 change reg_voltage to signed integer
2020-09-08 change processor frequency to 72MHz to make it easy to generate 30kHz timer clock. This makes our drive frequency 300Hz which is more resilient to 60Hz and 50Hz noise. also means our spi frequency re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
2020-09-14 added annotation to schematic indicating which UMCC-UMCC cables to use
2020-09-19 add code to automatically snap signal back to 48 if it goes out of bounds
2020-09-19 add ref calibration mode, triggered by receiving the letter 'c' over serial. Also keep retrying CDC transmit if USB is busy
2020-09-20 stream and plot reference voltage
2020-09-20 doubel buffer signal and reference data in order to prevent overwriting data before it is transmitted
2020-09-20 plot demod data rather than just pritning it
2020-09-20 remove old view script
2020-09-20 add code to generate calibration table for ref
2020-09-20 calcualte the average reg step
2020-09-20 subtract offset from data in viewer.py based on average step per dac code
2020-10-26 add bias tester design
2020-10-26 add AD822x breakout design
2020-11-29 simple commands over serial to enable/disable drive and enter reference calibration mode
2020-11-29 add command to soft reset chip
2020-11-29 adjust reference voltage once per packet and use the average value to target our target value. This prevents oscillation due to noise
2020-11-29 add commnds to enter bootloader from code. When magic SRAM variable is equalt oc ertain number, code jumps into bootloader before doing anything else
2020-11-30 add pingpong script
2020-11-30 miscellaneous file updated
2020-11-30 small updates
2020-11-30 reorder spi transactions so that signal is read before adjusting reference
2020-11-30 add more python tools
2020-11-30 add eoglass2.1 kicad files
2020-11-30 add kicad files for nose bridge pcb
2020-11-30 add files for UFL->Electrode adapter
2020-11-30 add data collected for EOGlass2
2020-11-30 add script to plot multiple data captures
2020-11-30 add script to simulate sense signal waveform and decoding
2020-11-30 add old script for beeping dots
2020-11-30 add random step file forr kicad
2020-11-30 add script to analyse phae of 300Hz signal on EOG data
2020-12-07 added files for calculating RC filter on ADC
2020-12-07 update signal RC filter to have component vlaues
2021-01-19 added fakeeyes design
2021-01-19 add fakeeyes schematic as pdf

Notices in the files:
parts and their libraries:
Copyright 2016 Accelerated Designs. All rights reserved.
